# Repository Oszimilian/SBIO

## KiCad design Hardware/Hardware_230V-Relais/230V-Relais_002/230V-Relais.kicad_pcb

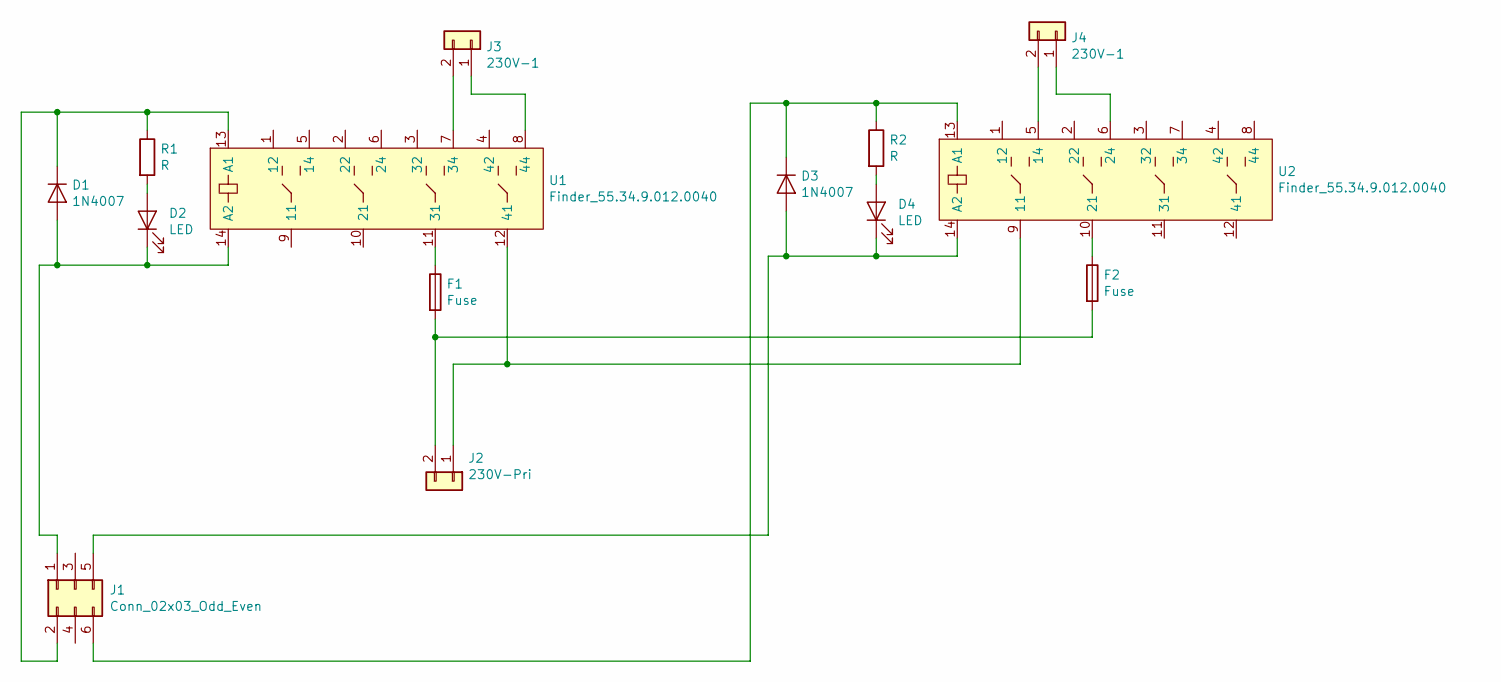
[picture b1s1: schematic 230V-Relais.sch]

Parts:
D1, D3: 1N4007; D_DO-41_SOD81_P10.16mm_Horizontal
D2, D4: LED; LED_D3.0mm
F1, F2: Fuse; Fuseholder_Cylinder-5x20mm_Schurter_0031_8201_Horizontal_Op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
J1: Conn_02x03_Odd_Even; Wanne_6Pol
J2: 230V-Pri; PhoenixContact_MSTBA_2,5_2-G-5,08_1x02_P5.08mm_Horizontal
J3, J4: 230V-1; PhoenixContact_MSTBA_2,5_2-G-5,08_1x02_P5.08mm_Horizontal
R1, R2: R; R_0805_2012Metric_Pad1.15x1.40mm_HandSolder
U1, U2: Finder_55.34.9.012.0040; Finder-55.34.012.0040

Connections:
unnamed: D1.1 (K), J1.2, R1.1, U1.13 (A1)
unnamed: D1.2 (A), D2.1 (K), J1.1, U1.14 (A2)
unnamed: D2.2 (A), R1.2
unnamed: D3.1 (K), J1.6, R2.1, U2.13 (A1)
unnamed: D3.2 (A), D4.1 (K), J1.5, U2.14 (A2)
unnamed: D4.2 (A), R2.2
unnamed: F1.1, U1.11 (31)
unnamed: F1.2, F2.2, J2.2
unnamed: F2.1, U2.10 (21)
unnamed: J2.1, U1.12 (41), U2.9 (11)
unnamed: J3.1, U1.8 (44)
unnamed: J3.2, U1.7 (34)
unnamed: J4.1, U2.6 (24)
unnamed: J4.2, U2.5 (14)

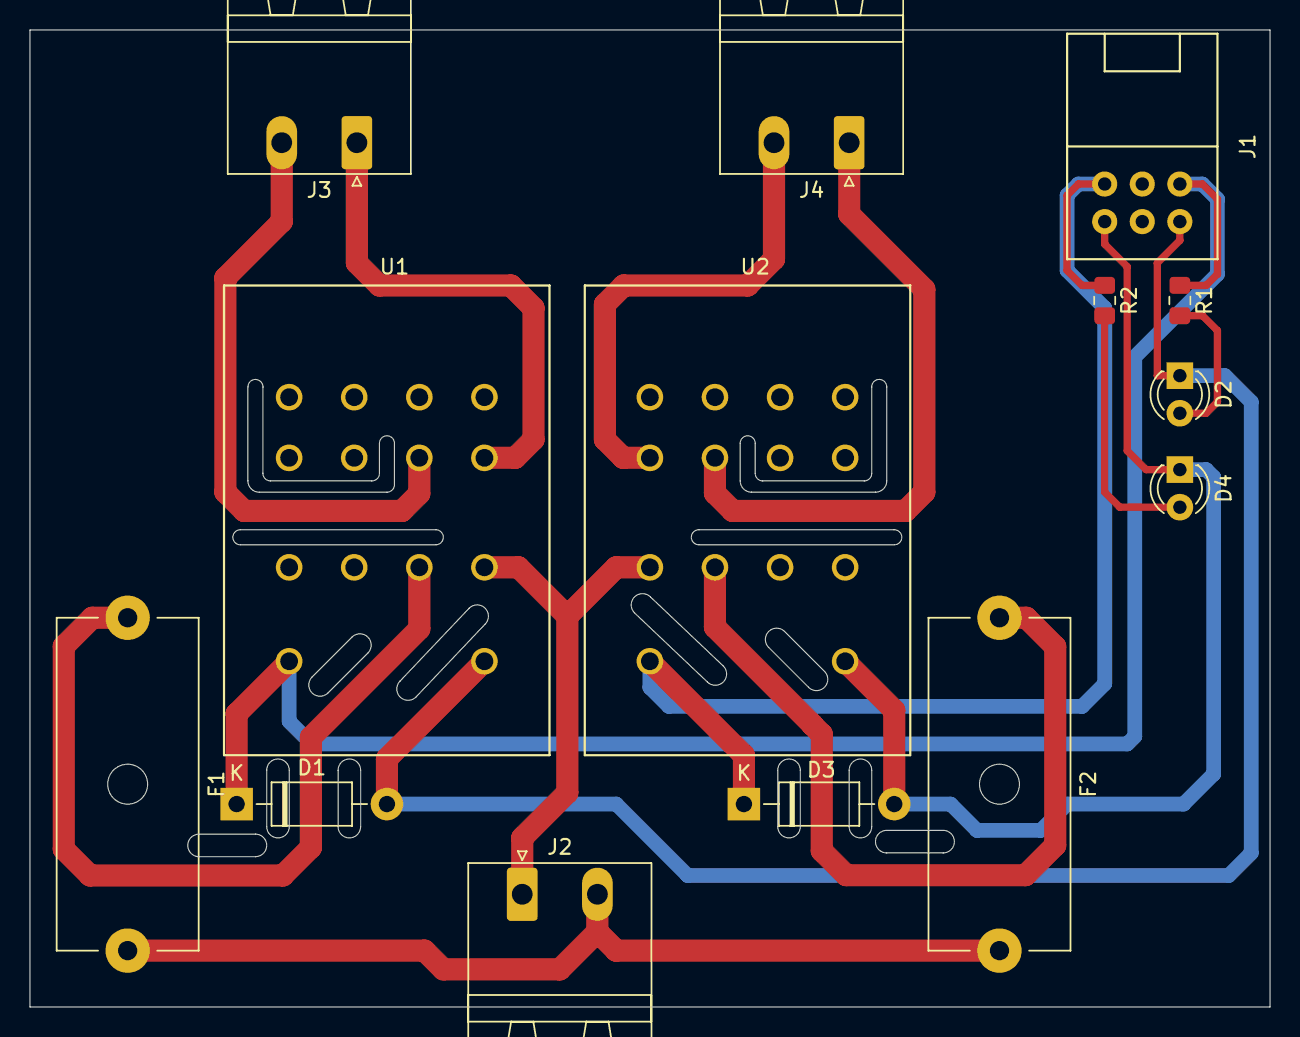
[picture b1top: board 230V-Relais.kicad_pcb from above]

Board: 2 copper layers, 83.8 x 66.0 mm, 14 parts (0 on the bottom side), 14 nets.

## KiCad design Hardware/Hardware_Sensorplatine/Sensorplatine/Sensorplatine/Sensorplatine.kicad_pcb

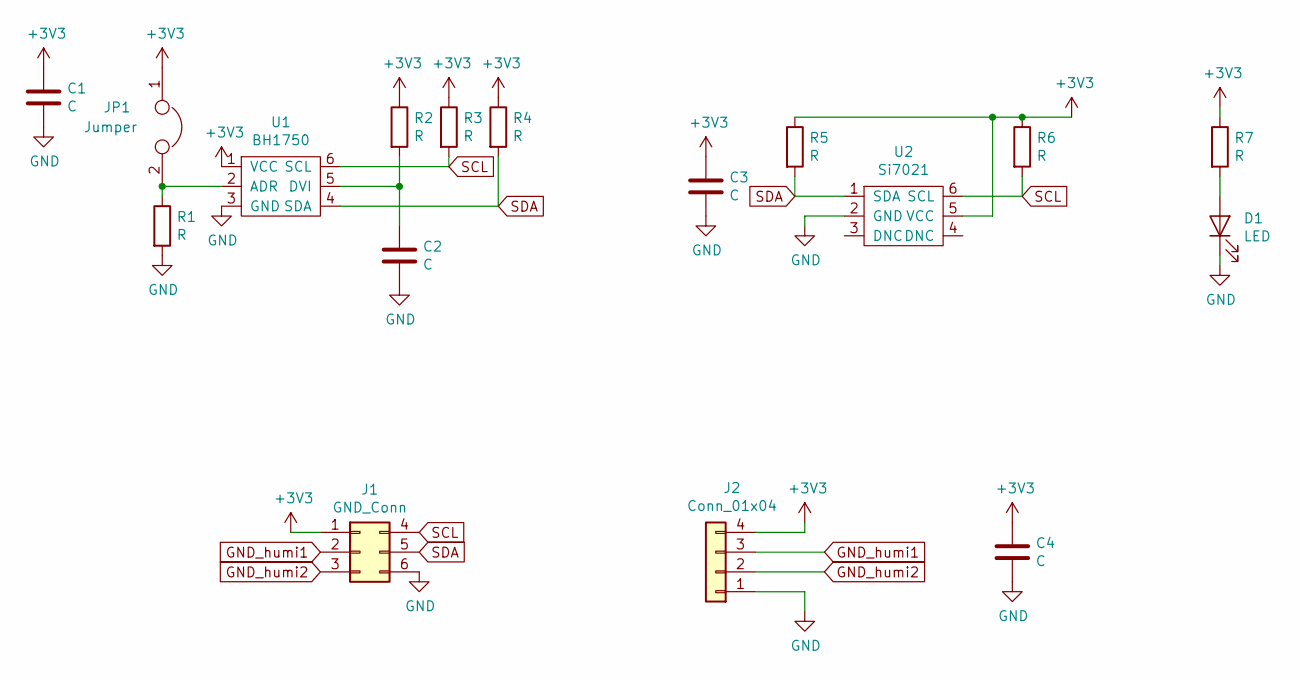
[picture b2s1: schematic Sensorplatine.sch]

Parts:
C1, C2, C3, C4: C; C_0603_1608Metric_Pad1.05x0.95mm_HandSolder
D1: LED; LED_0805_2012Metric_Pad1.15x1.40mm_HandSolder
J1: GND_Conn; PinSocket_2x03_P2.54mm_Vertical
J2: Conn_01x04; PinHeader_1x04_P2.54mm_Vertical
JP1: Jumper; SolderJumper-2_P1.3mm_Open_RoundedPad1.0x1.5mm
R1, R2, R3, R4, R5, R6, R7: R; R_0603_1608Metric_Pad1.05x0.95mm_HandSolder
U1: BH1750; Si7015
U2: Si7021; DFN-6-1EP_3x3mm_P1mm_EP1.5x2.4mm

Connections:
+3V3: C1.1, C3.1, C4.1, J1.1, J2.4, JP1.1, R2.1, R3.1, R4.1, R5.1, R6.1, R7.1, U1.1 (VCC), U2.5 (VCC)
GND: C1.2, C2.2, C3.2, C4.2, D1.1 (K), J1.6, J2.1, R1.2, U1.3 (GND), U2.2 (GND)
GND_humi1: J1.2, J2.3
GND_humi2: J1.3, J2.2
unnamed: C2.1, R2.2, U1.5 (DVI)
unnamed: D1.2 (A), R7.2
unnamed: JP1.2, R1.1, U1.2 (ADR)
SCL: J1.4, R3.2, R6.2, U1.6 (SCL), U2.6 (SCL)
SDA: J1.5, R4.2, R5.2, U1.4 (SDA), U2.1 (SDA)

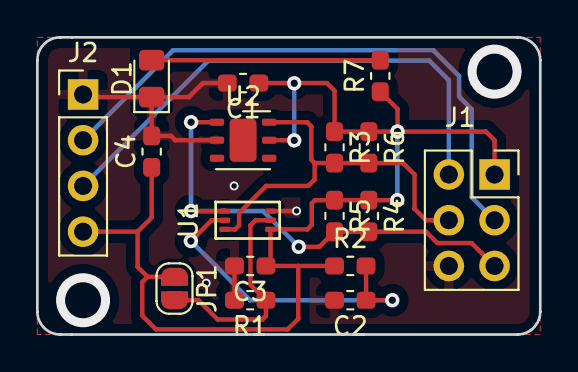
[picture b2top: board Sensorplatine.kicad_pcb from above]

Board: 2 copper layers, 27.9 x 16.5 mm, 17 parts (0 on the bottom side), 9 nets.

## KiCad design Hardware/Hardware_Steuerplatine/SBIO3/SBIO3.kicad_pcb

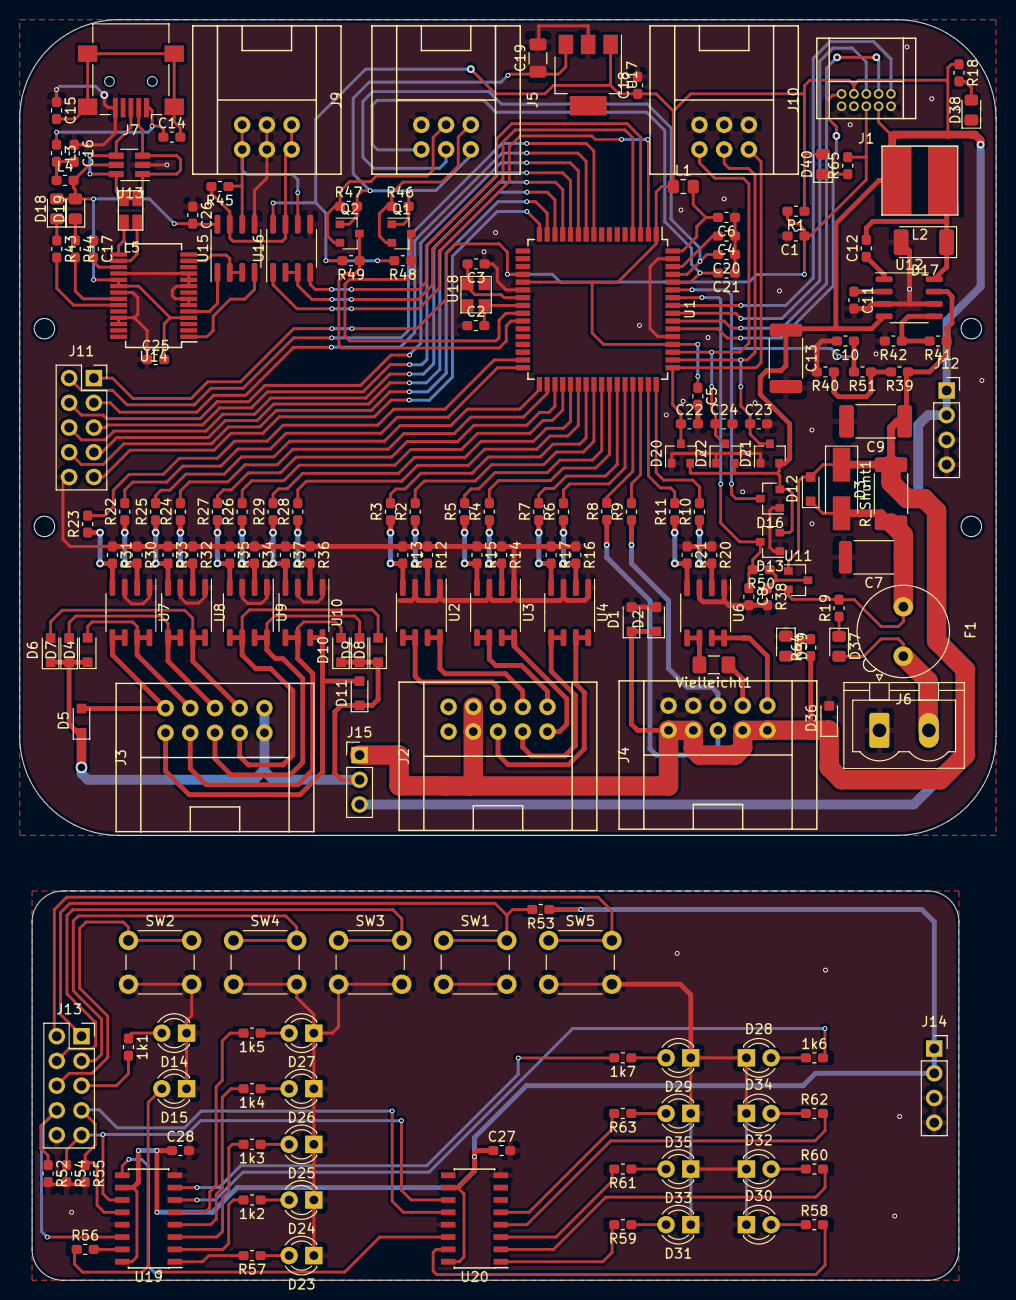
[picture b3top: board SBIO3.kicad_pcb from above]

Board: 2 copper layers, 100.3 x 129.5 mm, 188 parts (0 on the bottom side), 158 nets.

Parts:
1k1, 1k2, 1k3, 1k4, 1k5, 1k6, 1k7: R; R_0603_1608Metric_Pad1.05x0.95mm_HandSolder
C1, C4, C8, C10: 10nF; C_0603_1608Metric_Pad1.05x0.95mm_HandSolder
C2, C3: 22pF; C_0603_1608Metric_Pad1.05x0.95mm_HandSolder
C5, C6, C11, C12, C14, C15, C16, C17, C18, C20, C21, C25, C26: 100nF; C_0603_1608Metric_Pad1.05x0.95mm_HandSolder
C7, C13: 68uF; C_2512_6332Metric
C9: 68uF; C_2512_6332Metric_Pad1.52x3.35mm_HandSolder
C19: 10uF; C_1206_3216Metric
C22, C23, C24, C27, C28: C; C_0603_1608Metric_Pad1.05x0.95mm_HandSolder
D1, D2, D4, D5, D6, D7, D8, D9, D10, D11, D36: 1N4148; D_SOD-323_HandSoldering
D3: 1N4148; D_SMA_Handsoldering
D12: 1N4148
D13, D16, D20, D21, D22: BAS40-04; SOT-23
D14, D15, D23: Heizung; LED_D3.0mm
D17: D_Schottky_Small; MAX5035_50SQ100
D18, D19, D37, D38, D39, D40: LED; LED_0805_2012Metric_Pad1.15x1.40mm_HandSolder
D24: Lüfter; LED_D3.0mm
D25: Pumpe; LED_D3.0mm
D26: RGB; LED_D3.0mm
D27: SM; LED_D3.0mm
D28: LUMI_HIGH; LED_D3.0mm
D29: LUMI_LOW; LED_D3.0mm
D30: TEMP_HIGH; LED_D3.0mm
D31: TEMP_LOW; LED_D3.0mm
D32: HUMI_HIGH; LED_D3.0mm
D33: HUMI_LOW; LED_D3.0mm
D34: GNDHUMI_HIGH; LED_D3.0mm
D35: GNDHUMI_LOW; LED_D3.0mm
F1: Fuse; Fuseholder_TR5_Littelfuse_No560_No460
J1: AVR-JTAG-10; Con-JTAG
J2: RGB; Wanne-10Pol
J3: Con_SM; Wanne-10Pol
J4: Con_ALL; Wanne-10Pol
J5: Conn_02x03_Top_Bottom; Wanne_6Pol
J6: +12V; PhoenixContact_MSTBVA_2,5_2-G-5,08_1x02_P5.08mm_Vertical
J7: USB_B_Mini; USB_Mini-B_Lumberg_2486_01_Horizontal
J9: RS485; Wanne_6Pol
J10: Inputs; Wanne_6Pol
J11, J13: Frontpannel; PinSocket_2x05_P2.54mm_Vertical
J12, J14: Conn_01x04; PinSocket_1x04_P2.54mm_Vertical
J15: Jumper; PinHeader_1x03_P2.54mm_Vertical
L1: 10uH; L_0805_2012Metric_Pad1.15x1.40mm_HandSolder
L2: L; MAX5035_100uH_Coil
L3, L4: L; L_0603_1608Metric_Pad1.05x0.95mm_HandSolder
L5: WE-CNSW
Q1, Q2: BS170F; SOT-23
R1, R65: R; R_0603_1608Metric_Pad1.05x0.95mm_HandSolder
R2, R3, R4, R5, R6, R7, R8, R9, R10, R11, R22, R23, R24, R25, R26, R27, R28, R29: 160R; R_0603_1608Metric_Pad1.05x0.95mm_HandSolder
R12, R13, R14, R15, R16, R17, R20, R21, R30, R31, R32, R33, R34, R35, R36, R37, R46, R47, R48, R49, R52, R53, R54, R55: 10k; R_0603_1608Metric_Pad1.05x0.95mm_HandSolder
R18, R19, R38, R64: 5k; R_0603_1608Metric_Pad1.05x0.95mm_HandSolder
R39: 470k; R_0603_1608Metric_Pad1.05x0.95mm_HandSolder
R40: 120k; R_0603_1608Metric_Pad1.05x0.95mm_HandSolder
R41, R42: 510k; R_0603_1608Metric_Pad1.05x0.95mm_HandSolder
R43, R44, R56, R57, R58, R59, R60, R61, R62, R63: 1k; R_0603_1608Metric_Pad1.05x0.95mm_HandSolder
R45: 120R; R_0603_1608Metric_Pad1.05x0.95mm_HandSolder
R50, R51: 100k; R_0603_1608Metric_Pad1.05x0.95mm_HandSolder
R_Shunt1: 125mOhm; R_2512_6332Metric_Pad1.52x3.35mm_HandSolder
SW1, SW2, SW3, SW4, SW5: SW_DIP_x01; SW_PUSH_6mm
U1: ATmega64-16AU; TQFP-64_14x14mm_P0.8mm
U2, U3, U4, U6, U7, U8, U9, U10: IRF9313PBF; SO-8_3.9x4.9mm_P1.27mm
U11: ZXCT1109; SOT-23
U12: MAX_5035_BUSA; SO-8_3.9x4.9mm_P1.27mm
U13: WE_TVS; SOT-23-6_Handsoldering
U14: FT232RL_2; SSOP-28_5.3x10.2mm_P0.65mm
U15, U16: MAX3072E; SOIC-8_3.9x4.9mm_P1.27mm
U17: LM2936-3.3; SOT-223
U18: 16Mhz-Quarz-Small; 16Mhz Quarz Small
U19, U20: 74HC595; SOIC-16_3.9x9.9mm_Pitch1.27mm
Vielleicht1: R; R_1206_3216Metric_Pad1.42x1.75mm_HandSolder

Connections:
+3V3: C19.1, J5.1, Q1.1, Q2.1, R46.2, R47.2, U17.3
+5C: C25.2, C26.2, D18.2, D19.2, L4.2, U13.5, U14.4, U14.19, U14.20, U15.8
+5V: C5.1, C13.1, C18.1, C27.1, C28.1, D13.2, D16.2, D20.2, D21.2, D22.2, D40.2, J1.4, J1.7, J12.1, J12.2, J14.1, J14.2, J15.3, L1.1, L2.2, R1.1, R18.1, R48.2, R49.2, R53.1, U1.1, U1.21, U1.52, U12.4, U16.8, U17.1, U19.10, U19.16, U20.10, U20.16
+12V: C9.1, D1.1, D2.1, D3.1, D12.2, D36.1, J2.2, J2.7, J4.6, J4.7, J4.9, J4.10, J15.1, R39.1, R41.1, R64.1, R_Shunt1.2, U11.1, U12.7
/Frontpannel/Dbg1-: J13.6, SW2.1
/Frontpannel/Dbg2-: 1k1.2, J13.5
/Frontpannel/NOTAUS-: J13.2, SW5.1
/Frontpannel/RESET-: J13.1, R53.2, SW1.1
/Frontpannel/SR_Daten-: J13.8, R52.1, U19.14
/Frontpannel/SR_Latch-: J13.7, R55.1, U19.12, U20.12
/Frontpannel/SR_Takt-: J13.9, R54.1, U19.11, U20.11
/Frontpannel/START-: J13.4, SW3.1
/Frontpannel/STOP-: J13.3, SW4.1
Current_Controle: C8.1, D13.3, R50.2, U1.58
Dbg1: J11.6, U1.13
Dbg2: J11.5, U1.12
GND: C1.2, C2.1, C3.1, C4.1, C5.2, C6.1, C7.2, C8.2, C9.2, C10.2, C11.2, C13.2, C15.1, C16.1, C17.1, C18.2, C19.2, C20.1, C21.1, C22.2, C23.2, C24.2, C25.1, C26.1, C27.2, C28.2, D1.2, D2.2, D13.1, D14.1, D15.1, D16.1, D17.2, D20.1, D21.1, D22.1, D23.1, D24.1, D25.1, D26.1, D27.1, D28.1, D29.1, D30.1, D31.1, D32.1, D33.1, D34.1, D35.1, D36.2, D38.1, D39.1, J1.2, J1.10, J4.1, J4.2, J5.6, J6.1, J7.5, J9.2, J9.5, J10.4, J10.5, J10.6, J11.10, J12.3, J12.4, J13.10, J14.3, J14.4, R12.1, R13.1, R14.1, R15.1, R16.1, R17.1, R20.1, R21.1, R30.1, R31.1, R32.1, R33.1, R34.1, R35.1, R36.1, R37.1, R38.2, R40.2, R42.2, R52.2, R54.2, R55.2, SW1.2, SW2.2, SW3.2, SW4.2, SW5.2, U1.22, U1.53, U1.63, U2.1, U2.3, U3.1, U3.3, U4.1, U4.3, U6.1, U6.3, U7.1, U7.3, U8.1, U8.3, U9.1, U9.3, U10.1, U10.3, U12.3, U12.6, U13.2, U14.6, U14.7, U14.9, U14.10, U14.11, U14.18, U14.21, U14.25, U14.26, U15.5, U16.5, U17.2, U19.8, U19.13, U20.8, U20.13
GND_HUMI1: C20.2, J5.2, U1.61
GND_HUMI2: C21.2, J5.3, U1.60
HEIZUNG: R11.2, U1.47
INPUT1: C24.1, D22.3, J10.3, U1.51
INPUT2: C23.1, D21.3, J10.2, U1.50
I²C_SCL: Q1.3, R48.1, U1.25
I²C_SDA: Q2.3, R49.1, U1.26
NOT-AUS: C22.1, D20.3, J10.1, U1.49
NOTAUS: J11.2, U1.9
unnamed: 1k1.1, D14.2
unnamed: 1k2.1, D24.2
unnamed: 1k2.2, U19.2
unnamed: 1k3.1, D25.2
unnamed: 1k3.2, U19.3
unnamed: 1k4.1, D26.2
unnamed: 1k4.2, U19.4
unnamed: 1k5.1, D27.2
unnamed: 1k5.2, U19.5
unnamed: 1k6.1, D28.2
unnamed: 1k6.2, U19.6
unnamed: 1k7.1, D29.2
unnamed: 1k7.2, U19.7
unnamed: C2.2, U1.24, U18.2
unnamed: C3.2, U1.23, U18.4
unnamed: C4.2, U1.62
unnamed: C6.2, L1.2, U1.64
unnamed: C7.1, D3.2, D12.1, F1.1, R19.2, R_Shunt1.1, U11.2
unnamed: C11.1, U12.2
unnamed: C12.1, U12.1
unnamed: C12.2, D17.1, L2.1, U12.8
unnamed: C14.1, J7.1, L3.1
unnamed: C14.2, C15.2, J7.6
unnamed: C16.2, L3.2, L4.1
unnamed: C17.2, U14.17
unnamed: D4.2, J3.2, U7.7, U7.8
unnamed: D5.2, J3.1, U7.5, U7.6
unnamed: D6.2, J3.4, U8.7, U8.8
unnamed: D7.2, J3.3, U8.5, U8.6
unnamed: D8.2, J3.9, U9.5, U9.6
unnamed: D9.2, J3.8, U9.7, U9.8
unnamed: D4.1, D5.1, D6.1, D7.1, D8.1, D9.1, D10.1, D11.1, J3.5, J3.10, J15.2
unnamed: D10.2, J3.7, U10.5, U10.6
unnamed: D11.2, J3.6, U10.7, U10.8
unnamed: D15.2, R56.1
unnamed: D18.1, R43.1
unnamed: D19.1, R44.1
unnamed: D23.2, R57.1
unnamed: D30.2, R58.1
unnamed: D31.2, R59.1
unnamed: D32.2, R60.1
unnamed: D33.2, R61.1
unnamed: D34.2, R62.1
unnamed: D35.2, R63.1
unnamed: D37.1, R19.1
unnamed: D37.2, F1.2, J6.2
unnamed: D38.2, R18.2
unnamed: D39.2, R64.2
unnamed: D40.1, R65.1
unnamed: J2.3, U2.5, U2.6
unnamed: J2.4, U2.7, U2.8
unnamed: J2.5, U3.5, U3.6
unnamed: J2.8, U4.7, U4.8
unnamed: J2.9, U4.5, U4.6
unnamed: J2.10, U3.7, U3.8
unnamed: J4.3, R9.1
unnamed: J4.4, Vielleicht1.1
unnamed: J4.5, U6.7, U6.8
unnamed: J4.8, R8.1
unnamed: J5.4, Q1.2, R46.1
unnamed: J5.5, Q2.2, R47.1
unnamed: J7.2, L5.3, U13.1, U13.3
unnamed: J7.3, L5.1, U13.4, U13.6
unnamed: J9.1, J9.4, R45.2, U15.7, U16.7
unnamed: J9.3, J9.6, R45.1, U15.6, U16.6
unnamed: L5.2, U14.15
unnamed: L5.4, U14.16
unnamed: R10.1, R20.2, U6.2
unnamed: R11.1, R21.2, U6.4
unnamed: R2.1, R12.2, U2.2
unnamed: R3.1, R13.2, U2.4
unnamed: R4.1, R14.2, U3.2
unnamed: R5.1, R15.2, U3.4
unnamed: R6.1, R16.2, U4.2
unnamed: R7.1, R17.2, U4.4
unnamed: R22.1, R30.2, U7.2
unnamed: R23.1, R31.2, U7.4
unnamed: R24.1, R32.2, U8.2
unnamed: R25.1, R33.2, U8.4
unnamed: R26.1, R34.2, U9.2
unnamed: R27.1, R35.2, U9.4
unnamed: R28.1, R36.2, U10.2
unnamed: R29.1, R37.2, U10.4
unnamed: R38.1, R50.1, U11.3
unnamed: R39.2, R40.1, R51.1
unnamed: R41.2, R42.1, U12.5
unnamed: R43.2, U14.23
unnamed: R44.2, U14.22
unnamed: R56.2, U19.15
unnamed: R57.2, U19.1
unnamed: R58.2, U20.15
unnamed: R59.2, U20.1
unnamed: R60.2, U20.2
unnamed: R61.2, U20.3
unnamed: R62.2, U20.4
unnamed: R63.2, U20.5
unnamed: U6.5, U6.6, Vielleicht1.2
unnamed: U14.1, U15.4
unnamed: U14.5, U15.1
unnamed: U14.13, U15.2, U15.3
unnamed: U19.9, U20.14
PWM_LUEFTER1: R9.2, U1.46
PWM_LUEFTER2: R8.2, U1.45
PWM_PUMPE: R10.2, U1.48
RESET: C1.1, J1.6, J11.1, R1.2, R65.2, U1.20
RGB1_BLAU: R3.2, U1.39
RGB1_GRUEN: R2.2, U1.40
RGB1_ROT: R5.2, U1.41
RGB2_BLAU: R4.2, U1.42
RGB2_GRUEN: R7.2, U1.43
RGB2_ROT: R6.2, U1.44
SM1_1: R22.2, U1.32
SM1_2: R23.2, U1.31
SM1_3: R24.2, U1.34
SM1_4: R25.2, U1.33
SM2_1: R26.2, U1.36
SM2_2: R27.2, U1.35
SM2_3: R28.2, U1.38
SM2_4: R29.2, U1.37
SR_Daten: J11.8, U1.15
SR_Latch: J11.7, U1.14
SR_Takt: J11.9, U1.16
Start: J11.4, U1.11
Stop: J11.3, U1.10
TCK: J1.1, U1.57
TDI: J1.9, U1.54
TDO: J1.3, U1.55
TMS: J1.5, U1.56
UART_DIR: U1.4, U16.2, U16.3
UART_RXD: U1.2, U16.1
UART_TXD: U1.3, U16.4
Voltage_Controle: C10.1, D16.3, R51.2, U1.59

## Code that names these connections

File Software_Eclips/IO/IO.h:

#define ON 			1
#define OFF 		0

#define Debounce	10

#define PWM_Anzahl	10

#define PWM_Pumpe 		0
#define PWM_Heizung 	1
#define PWM_Lufter1		2
#define PWM_Lufter2		3
#define PWM_Rot1		4
#define PWM_Grun1		5
#define PWM_Blau1		6
#define PWM_Rot2		7
#define PWM_Grun2		8
#define PWM_Blau2		9

typedef struct
{

	volatile uint8_t PWM_List[PWM_Anzahl];
	volatile  uint8_t PWM_Enabel[PWM_Anzahl];
	volatile uint8_t PWM_Wert[PWM_Anzahl];

}PWM_Setting;
PWM_Setting PWM;


//Input Ports & Pins
#define Input1_Port		PINA
#define Input2_Port		PINA
#define Stop_Port		PINB
#define Start_Port		PINB
#define NotAus_Port		PINE
#define DBG1_Port		PINB

#define Input1			0
#define Input2			1
#define Stop			0
#define Start			1
#define NotAus			7
#define DBG1			3


//Aktoren
#define Pumpe 		3
#define Heizung 	4
#define Lufter1		5
#define Lufter2		6


//RGB
#define Rot1		6
#define Grun1		5
#define Blau1		4

#define Rot2		7
#define Grun2		2
#define Blau2		7


//Schieberegister
#define Takt		4
#define Daten		5
#define Latch		6


//Schirttmotor 1
#define SM1_1		6
#define SM1_2		7
#define SM1_3		0
#define SM1_4		1


//Schrittmotor 2
#define SM2_1		0
#define SM2_2		1
#define SM2_3		2
#define SM2_4		3

//UART
#define DIR			2


//Schirttmotor 1 Schritte
#define SM1_Schritt1	PORTD |= (ON<<SM1_1);  PORTD &= ~(ON<<SM1_2); PORTG &= ~(ON<<SM1_3); PORTG &= ~(ON<<SM1_4);
#define SM1_Schritt2	PORTD &= ~(ON<<SM1_1); PORTD |= (ON<<SM1_2);  PORTG &= ~(ON<<SM1_3); PORTG &= ~(ON<<SM1_4);
#define SM1_Schritt3	PORTD &= ~(ON<<SM1_1); PORTD &= ~(ON<<SM1_2); PORTG |= (ON<<SM1_3);  PORTG &= ~(ON<<SM1_4);
#define SM1_Schritt4	PORTD &= ~(ON<<SM1_1); PORTD &= ~(ON<<SM1_2); PORTG &= ~(ON<<SM1_3); PORTG |= (ON<<SM1_4);


//Schirttmotor 2 Schritte
#define SM2_Schritt1	PORTC |= (ON<<SM2_1);  PORTC &= ~(ON<<SM2_2); PORTC &= ~(ON<<SM2_3); PORTC &= ~(ON<<S2_4);
#define SM2_Schritt2	PORTC &= ~(ON<<SM2_1); PORTC |= (ON<<SM2_2);  PORTC &= ~(ON<<S2_3);  PORTC &= ~(ON<<SM2_4);
#define SM2_Schritt3	PORTC &= ~(ON<<SM2_1); PORTC &= ~(ON<<SM2_2); PORTC |= (ON<<SM2_3);  PORTC &= ~(ON<<SM2_4);
#define SM2_Schritt4	PORTC &= ~(ON<<SM2_1); PORTC &= ~(ON<<SM2_2); PORTC &= ~(ON<<SM2_3); PORTC |= (ON<<SM2_4);


//GPIO Makros
#define _Pumpe(x) 		if (x) PORTA |= (1<<Pumpe);   else PORTA &= ~(1<<Pumpe);
#define _Heizung(x) 	if (x) PORTA |= (1<<Heizung); else PORTA &= ~(1<<Heizung);
#define _Lufter1(x)		if (x) PORTA |= (1<<Lufter1); else PORTA &= ~(1<<Lufter1);
#define _Lufter2(x)		if (x) PORTA |= (1<<Lufter2); else PORTA &= ~(1<<Lufter2);

#define _Rot1(x)		if (x) PORTC |= (1<<Rot1);    else PORTC &= ~(1<<Rot1);
#define _Grun1(x)		if (x) PORTC |= (1<<Grun1);   else PORTC &= ~(1<<Grun1);
#define _Blau1(x)		if (x) PORTC |= (1<<Blau1);   else PORTC &= ~(1<<Blau1);

#define _Rot2(x)		if (x) PORTA |= (1<<Rot2);    else PORTA &= ~(1<<Rot2);
#define _Grun2(x)		if (x) PORTG |= (1<<Grun2);   else PORTA &= ~(1<<Grun2);
#define _Blau2(x)		if (x) PORTC |= (1<<Blau2);   else PORTA &= ~(1<<Blau2);

#define _Latch(x)		if (x) PORTB |= (1<<Latch);   else PORTB &= ~(1<<Latch);
#define _Daten(x)		if (x) PORTB |= (1<<Daten);   else PORTB &= ~(1<<Daten);
#define _Takt(x)		if (x) PORTB |= (1<<Takt);    else PORTB &= ~(1<<Takt);

#define _DIR(x) 		if (x) PORTE |= (1<<DIR); 	  else PORTE &= ~(1<<DIR);


//Schrittmotor 1 Schritt
#define _SM1(x)		if (x==1) SM1_Schritt1 if (x==2) SM1_Schritt2 if (x==3) SM1_Schritt3 if (x==4) SM1_Schritt4
#define _SM2(x)		if (x==1) SM2_Schritt1 if (x==2) SM2_Schritt2 if (x==3) SM2_Schritt3 if (x==4) SM2_Schritt4




void Init_GPIO(PWM_Setting *PWM);

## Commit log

2021-06-11 ADD HEX
2021-06-12 not particular
2021-06-12 ADD
    Dont work at virtualbox VM
2021-06-12 ADD
    ADC
    UART
    Frontpanel
2021-06-13 ADD
    RX mit var dont work
2021-06-14 ADD
    solve
    thinks
2021-06-15 ADD
    -INFO
    -SRAM ausgedünnt
2021-06-15 Changes
    alles passt bis jetzt
2021-06-16 Delite
2022-03-03 für LEON
